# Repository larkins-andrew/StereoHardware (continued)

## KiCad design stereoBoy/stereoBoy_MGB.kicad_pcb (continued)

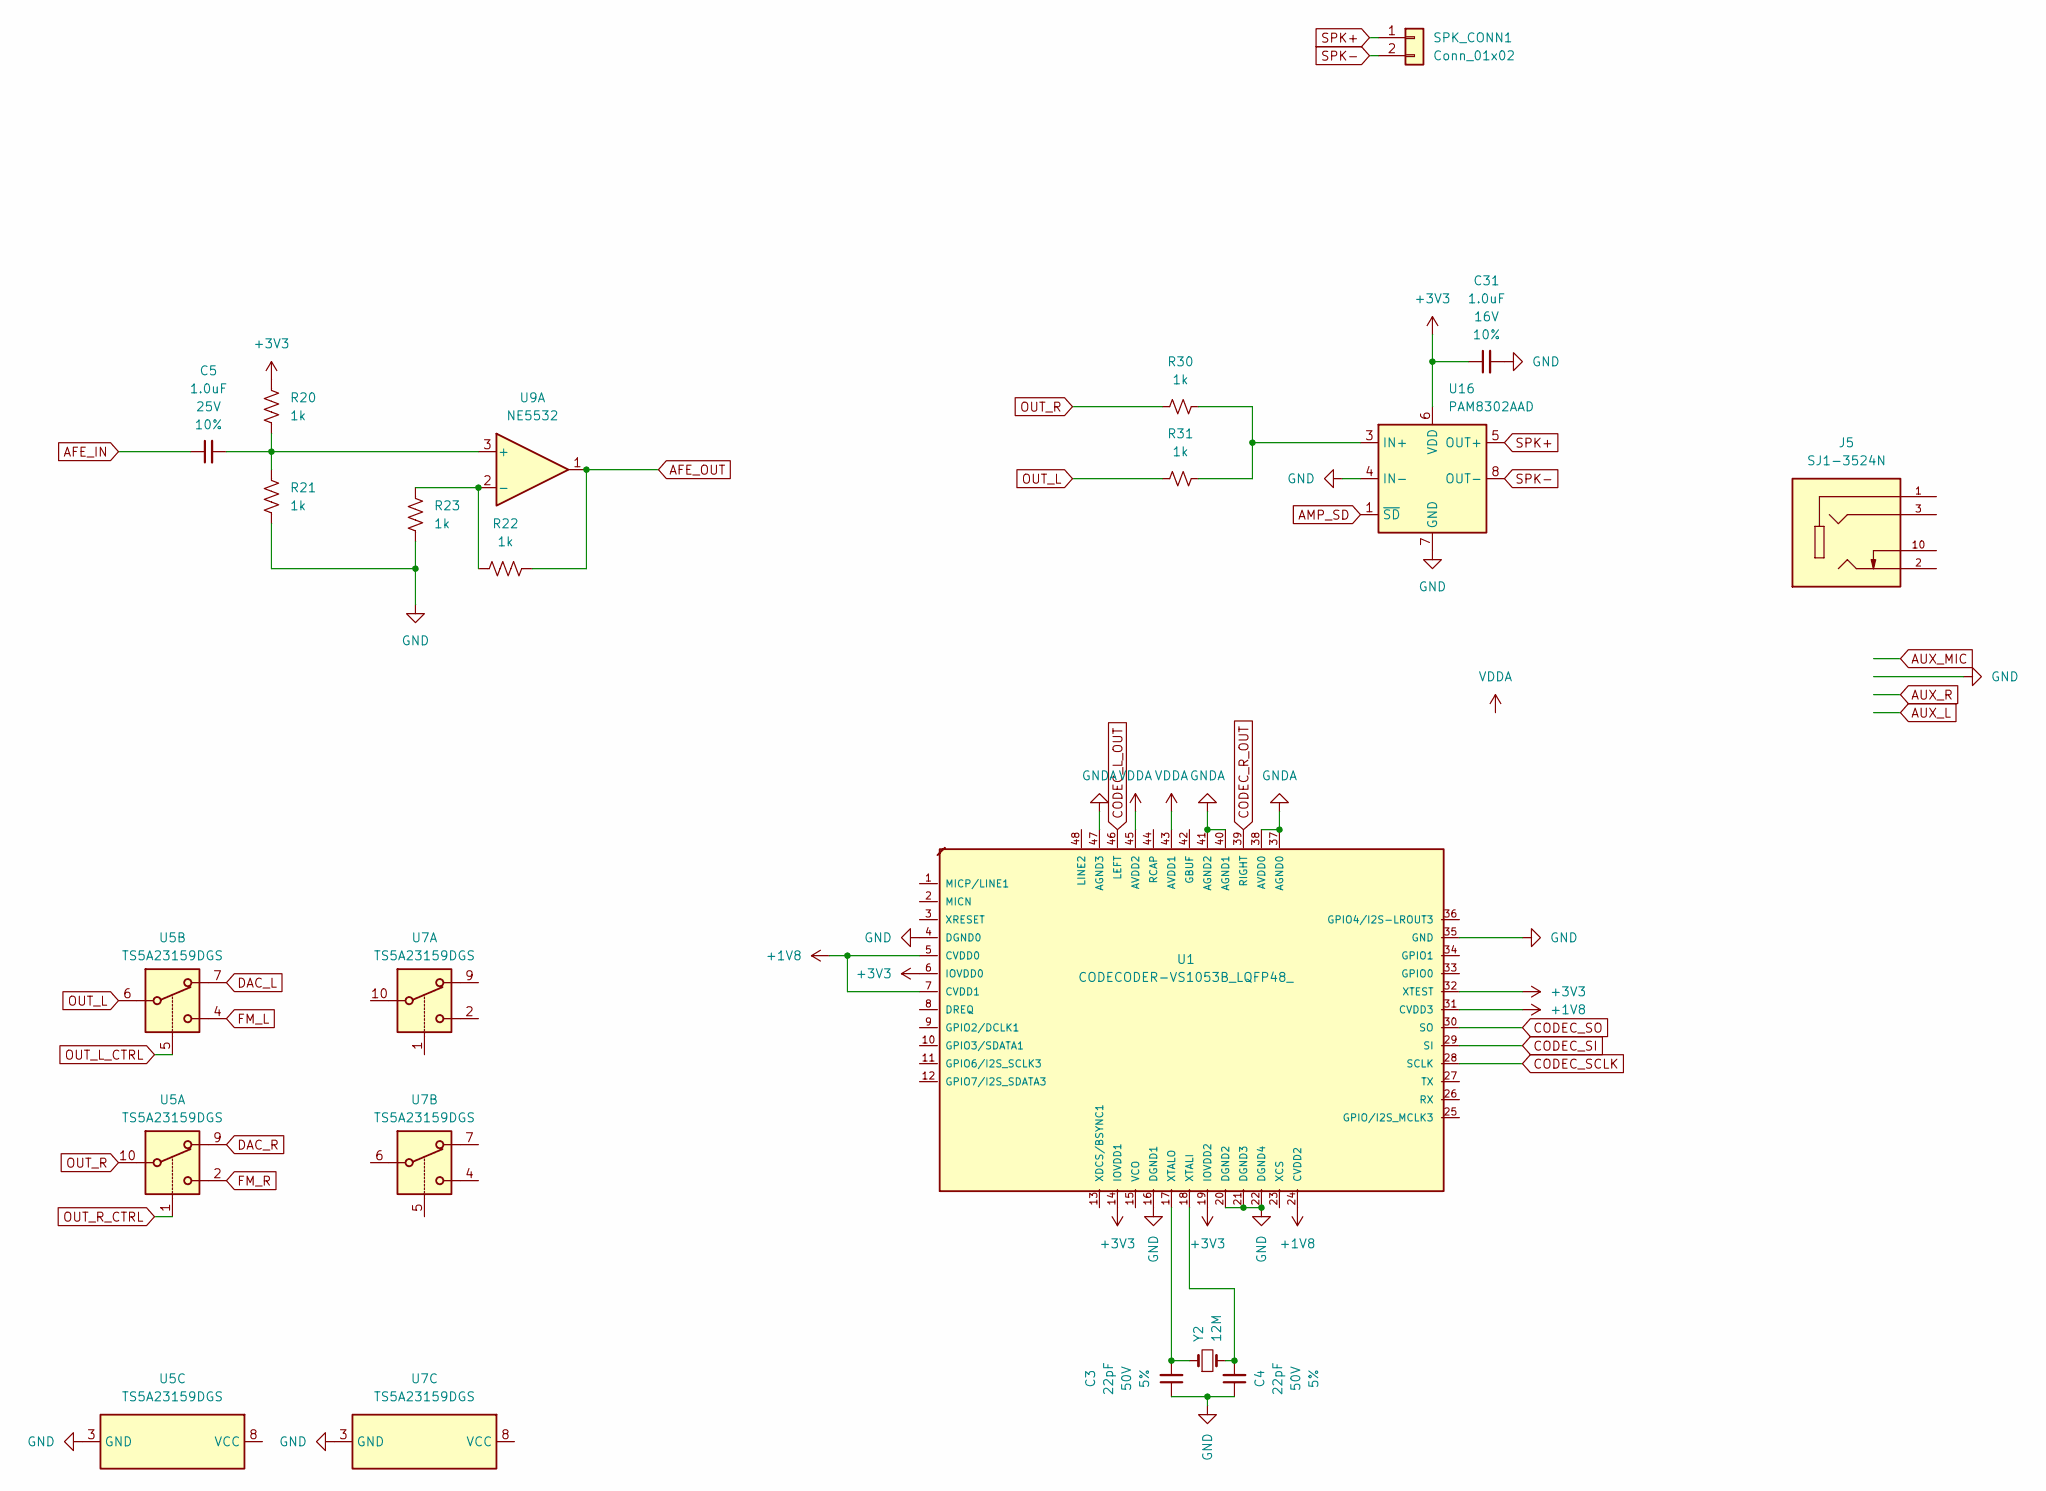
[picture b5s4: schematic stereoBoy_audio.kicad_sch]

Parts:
C3, C4: 22pF; C_0402_1005Metric; Voltage 50V; Tolerance 5%
C5: 1.0uF; C_0805_2012Metric; Voltage 25V; Tolerance 10%
C31: 1.0uF; C_0603_1608Metric; Voltage 16V; Tolerance 10%
J5: SJ1-3524N; PARTREV 1.05
R20, R21, R22, R23: 1k; R_0805_2012Metric
R30, R31: 1k; R_0603_1608Metric
SPK_CONN1: Conn_01x02; 1x02
U1: CODECODER-VS1053B_LQFP48_; VS1053b; MPN VS1053B
U5, U7: TS5A23159DGS; VSSOP-10_3x3mm_P0.5mm
U9: NE5532; SOIC-8_3.9x4.9mm_P1.27mm
U16: PAM8302AAD; MSOP-8_3x3mm_P0.65mm
Y2: 12M; Crystal_SMD_3.2x1.5mm

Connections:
+1V8: U1.5 (CVDD0), U1.7 (CVDD1), U1.24 (CVDD2), U1.31 (CVDD3); also elsewhere on the board
+3V3: C31.1, R20.1, U1.6 (IOVDD0), U1.14 (IOVDD1), U1.19 (IOVDD2), U1.32 (XTEST), U16.6 (VDD); also elsewhere on the board
AFE_IN: C5.1
AFE_OUT: R22.1, U9.1
AMP_SD: U16.1 (~SD)
CODEC_L_OUT: U1.46 (LEFT)
CODEC_R_OUT: U1.39 (RIGHT)
CODEC_SCLK: U1.28 (SCLK)
CODEC_SI: U1.29 (SI)
CODEC_SO: U1.30 (SO)
DAC_L: U5.7; also elsewhere on the board
DAC_R: U5.9; also elsewhere on the board
FM_L: U5.4
FM_R: U5.2
GND: C3.1, C4.1, C31.2, R21.2, R23.2, U1.4 (DGND0), U1.16 (DGND1), U1.20 (DGND2), U1.21 (DGND3), U1.22 (DGND4), U1.35 (GND), U5.3 (GND), U7.3 (GND), U16.4 (IN-), U16.7 (GND); also elsewhere on the board
GNDA: U1.37 (AGND0), U1.38 (AVDD0), U1.40 (AGND1), U1.41 (AGND2), U1.47 (AGND3); also elsewhere on the board
unnamed: C4.2, U1.18 (XTALI), Y2.2
unnamed: C3.2, U1.17 (XTALO), Y2.1
unnamed: C5.2, R20.2, R21.1, U9.3 (+)
unnamed: R22.2, R23.1, U9.2 (-)
unnamed: R30.2, R31.2, U16.3 (IN+)
OUT_L: R31.1, U5.6
OUT_L_CTRL: U5.5
OUT_R: R30.1, U5.10
OUT_R_CTRL: U5.1
SPK+: SPK_CONN1.1, U16.5 (OUT+)
SPK-: SPK_CONN1.2, U16.8 (OUT-)
VDDA: U1.43 (AVDD1), U1.45 (AVDD2); also elsewhere on the board

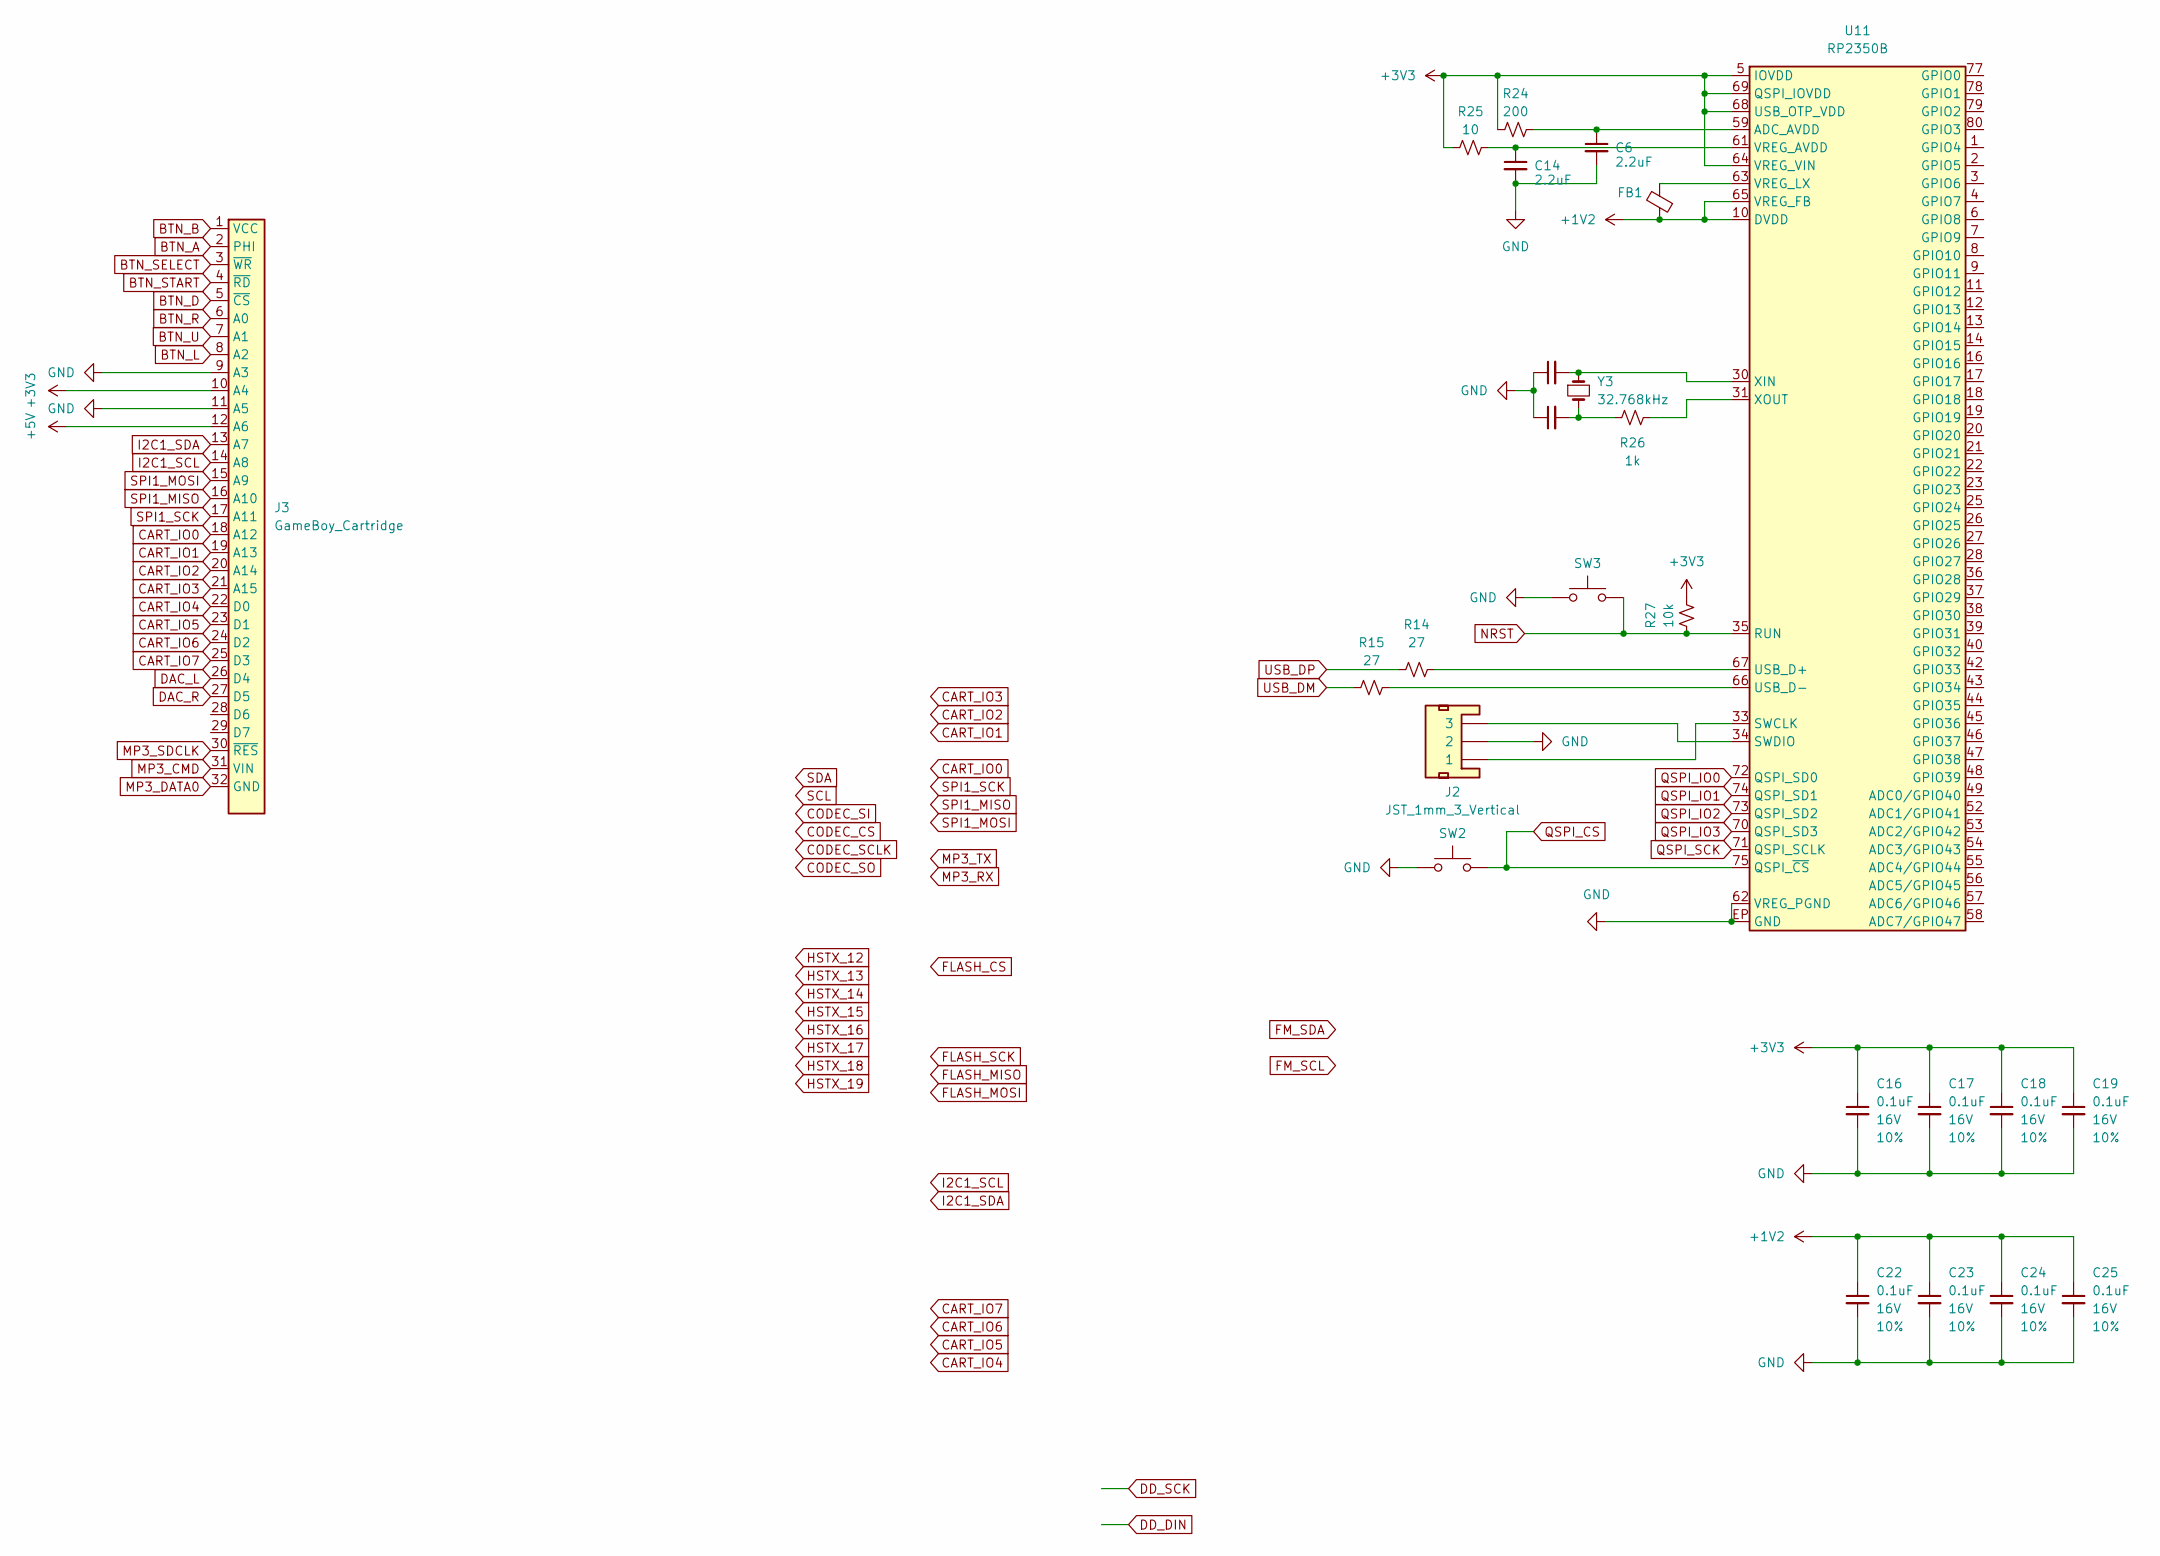
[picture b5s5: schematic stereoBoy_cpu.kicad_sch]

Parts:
C6, C14: 2.2uF; C_0402_1005Metric
C16, C17, C18, C19, C22, C23, C24, C25: 0.1uF; C_0402_1005Metric; Voltage 16V; Tolerance 10%
C20, C21: 18pF; C_0402_1005Metric; Voltage 50V; Tolerance 5%
FB1: FerriteBead_Small; L_0402_1005Metric
J2: JST_1mm_3_Vertical; JST_1x03_P1.0mm_Horizontal_SMD
J3: GameBoy_Cartridge; MGB-CART-CONN
R14, R15: 27; R_0402_1005Metric
R24: 200; R_0402_1005Metric
R25: 10; R_0402_1005Metric
R26: 1k; R_0402_1005Metric
R27: 10k; R_0603_1608Metric
SW2, SW3: SMD_4.2x3.2mm_h2.5mm; Push_SMD_4.2x3.2mm
U11: RP2350B; QFN-80-1EP_10x10mm_P0.4mm_EP3.4x3.4mm
Y3: 32.768kHz; Crystal_SMD_3.2x1.5mm

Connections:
+1V2: C22.1, C23.1, C24.1, C25.1, FB1.1, U11.10 (DVDD), U11.32 (DVDD), U11.51 (DVDD), U11.65 (VREG_FB)
+3V3: C16.1, C17.1, C18.1, C19.1, J3.10 (A4), R24.1, R25.1, R27.2, U11.5 (IOVDD), U11.15 (IOVDD), U11.24 (IOVDD), U11.29 (IOVDD), U11.41 (IOVDD), U11.50 (IOVDD), U11.60 (IOVDD), U11.64 (VREG_VIN), U11.68 (USB_OTP_VDD), U11.69 (QSPI_IOVDD), U11.76 (IOVDD); also elsewhere on the board
+5V: J3.12 (A6); also elsewhere on the board
BTN_A: J3.2 (PHI); also elsewhere on the board
BTN_B: J3.1 (VCC); also elsewhere on the board
BTN_D: J3.5 (~CS); also elsewhere on the board
BTN_L: J3.8 (A2); also elsewhere on the board
BTN_R: J3.6 (A0); also elsewhere on the board
BTN_SELECT: J3.3 (~WR); also elsewhere on the board
BTN_START: J3.4 (~RD); also elsewhere on the board
BTN_U: J3.7 (A1); also elsewhere on the board
CART_IO0: J3.18 (A12)
CART_IO1: J3.19 (A13)
CART_IO2: J3.20 (A14)
CART_IO3: J3.21 (A15)
CART_IO4: J3.22 (D0)
CART_IO5: J3.23 (D1)
CART_IO6: J3.24 (D2)
CART_IO7: J3.25 (D3)
DAC_L: J3.26 (D4); also elsewhere on the board
DAC_R: J3.27 (D5); also elsewhere on the board
GND: C6.2, C14.2, C16.2, C17.2, C18.2, C19.2, C20.1, C21.1, C22.2, C23.2, C24.2, C25.2, J2.2, J3.9 (A3), J3.11 (A5), SW2.1, SW3.1, U11.62 (VREG_PGND), U11.EP (GND); also elsewhere on the board
I2C1_SCL: J3.14 (A8)
I2C1_SDA: J3.13 (A7)
MP3_CMD: J3.31 (VIN)
MP3_DATA0: J3.32 (GND)
MP3_SDCLK: J3.30 (~RES)
NRST: R27.1, SW3.2, U11.35 (RUN)
unnamed: C21.2, R26.1, Y3.2
unnamed: C6.1, R24.2, U11.59 (ADC_AVDD)
unnamed: J2.1, U11.33 (SWCLK)
unnamed: J2.3, U11.34 (SWDIO)
unnamed: R14.2, U11.67 (USB_D+)
unnamed: R15.2, U11.66 (USB_D-)
unnamed: C14.1, R25.2, U11.61 (VREG_AVDD)
unnamed: FB1.2, U11.63 (VREG_LX)
unnamed: C20.2, U11.30 (XIN), Y3.1
unnamed: R26.2, U11.31 (XOUT)
QSPI_CS: SW2.2, U11.75 (QSPI_~CS)
QSPI_IO0: U11.72 (QSPI_SD0)
QSPI_IO1: U11.74 (QSPI_SD1)
QSPI_IO2: U11.73 (QSPI_SD2)
QSPI_IO3: U11.70 (QSPI_SD3)
QSPI_SCK: U11.71 (QSPI_SCLK)
SPI1_MISO: J3.16 (A10)
SPI1_MOSI: J3.15 (A9)
SPI1_SCK: J3.17 (A11)
USB_DM: R15.1; also elsewhere on the board
USB_DP: R14.1; also elsewhere on the board

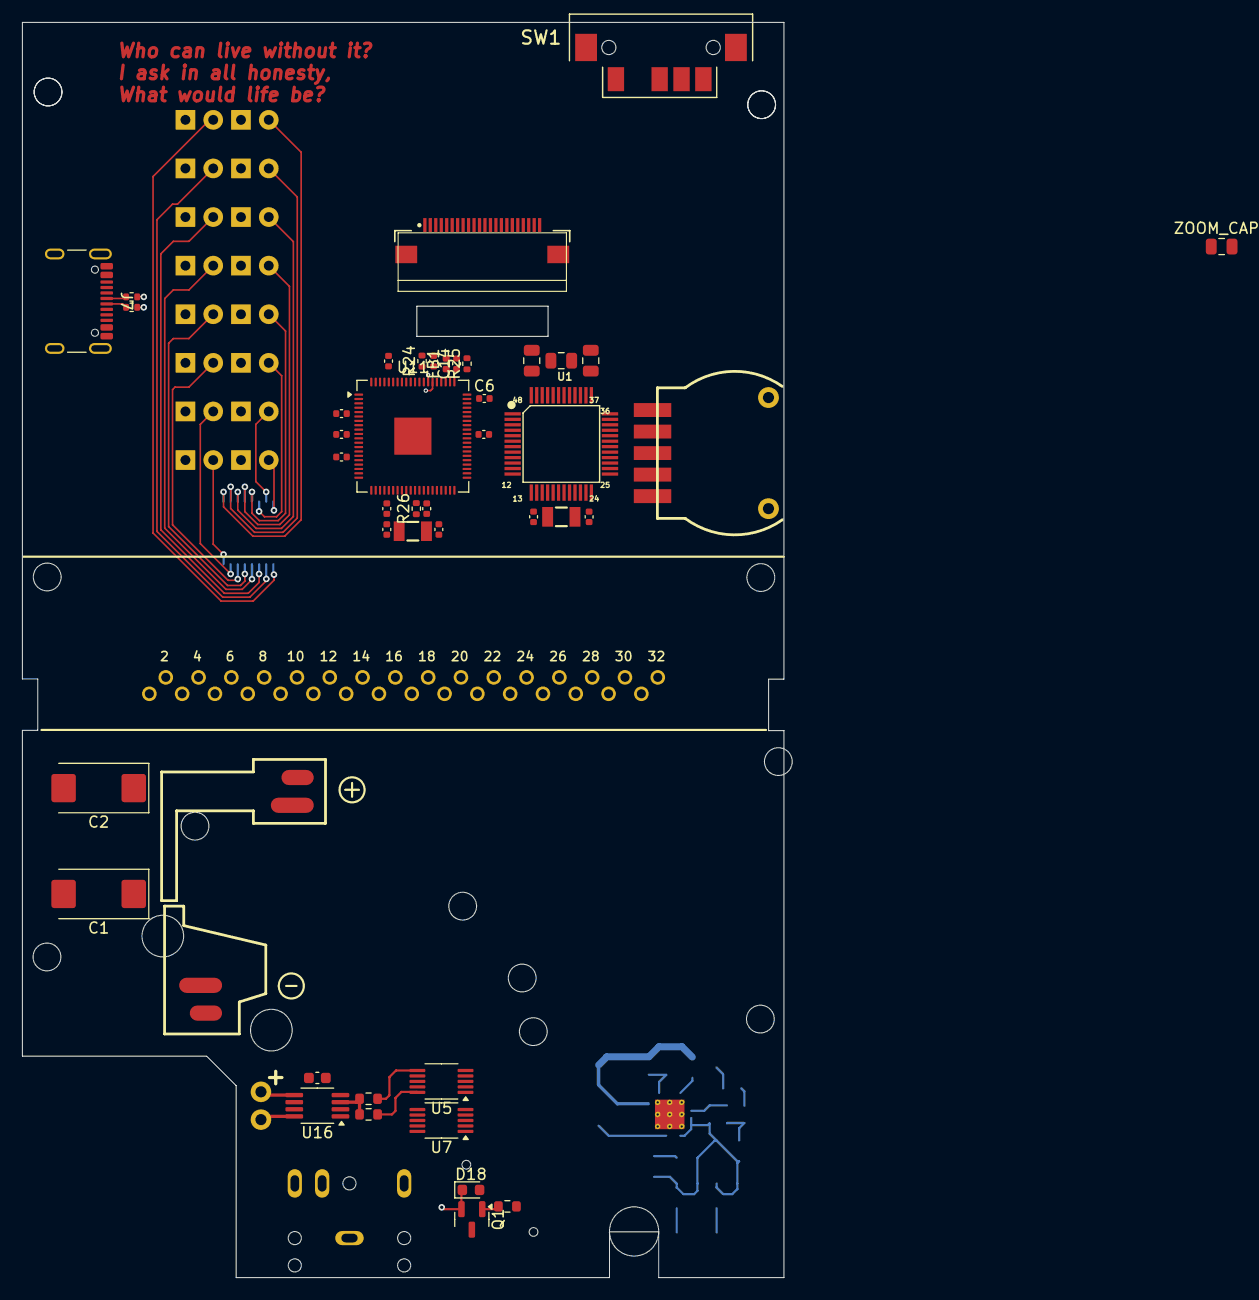
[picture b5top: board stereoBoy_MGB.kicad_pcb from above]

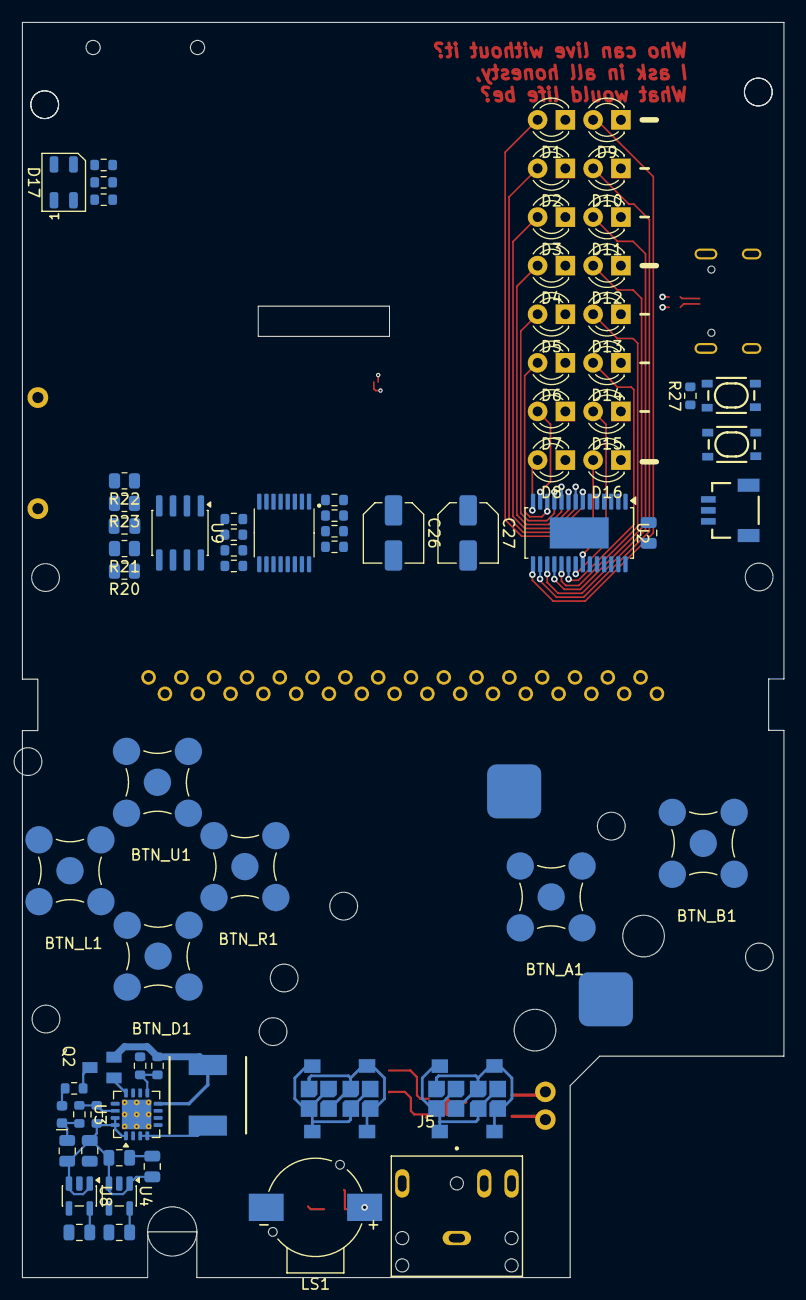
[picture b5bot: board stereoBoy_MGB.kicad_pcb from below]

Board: 4 copper layers, 69.6 x 114.8 mm, 130 parts (71 on the bottom side), 70 nets.

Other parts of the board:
1.54_IPS_LCD: 1.54_IPS_LCD
SW1: SMD_4.2x3.2mm_h2.5mm; MGB-SWITCH
UNK_HOLE_0: dummyfp0
UNK_HOLE_1: dummyfp1
UNK_HOLE_4: dummyfp4
UNK_HOLE_5: dummyfp5
UNK_HOLE_6: dummyfp6
UNK_HOLE_7: dummyfp7
UNK_HOLE_8: dummyfp8
UNK_HOLE_9: dummyfp9
UNK_HOLE_10: dummyfp10
UNK_HOLE_11: dummyfp11
UNK_HOLE_12: dummyfp12
UNK_HOLE_13: dummyfp13
VR1: MGB-POT

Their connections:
GND: VR1.P$1, VR1.P$6, VR1.P$7; also elsewhere on the board

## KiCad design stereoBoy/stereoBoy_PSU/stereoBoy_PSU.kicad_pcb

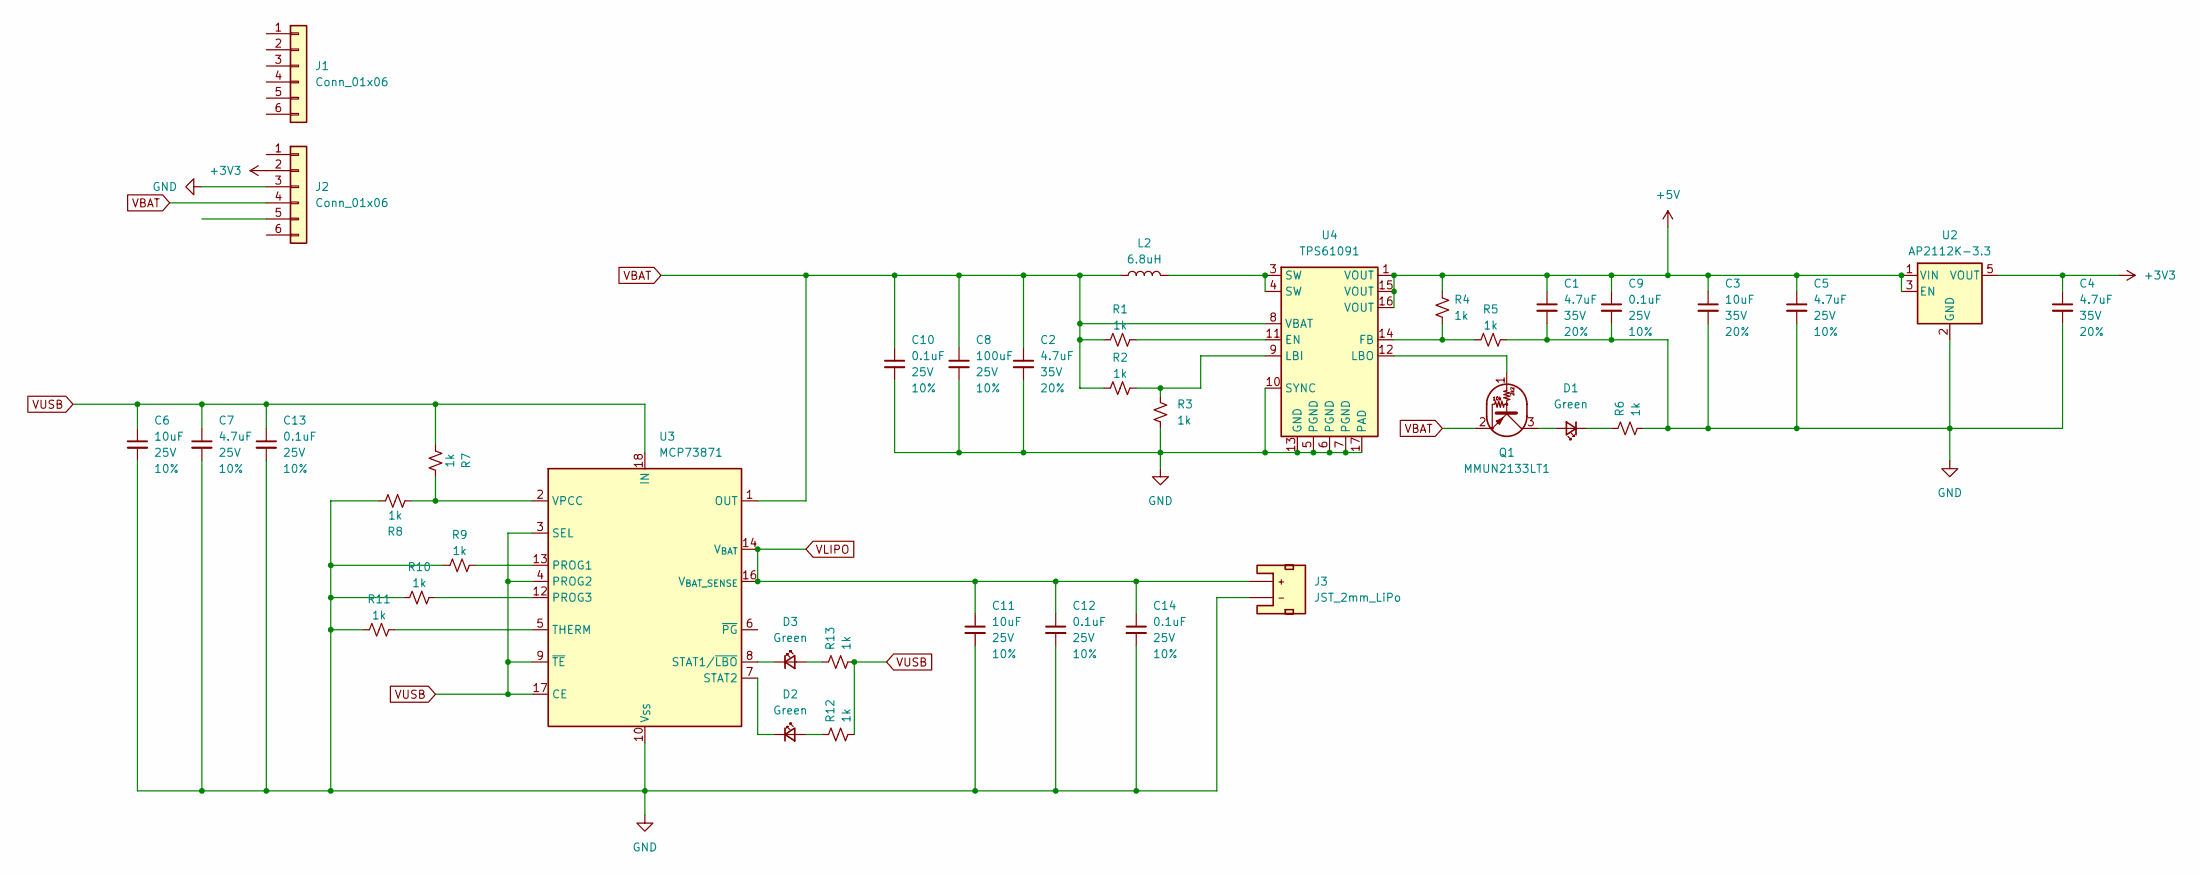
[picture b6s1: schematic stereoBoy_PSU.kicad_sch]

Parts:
C1, C2, C4: 4.7uF; C_0603_1608Metric; Voltage 35V; Tolerance 20%
C3: 10uF; C_0603_1608Metric; Voltage 35V; Tolerance 20%
C5, C7: 4.7uF; C_0805_2012Metric; Voltage 25V; Tolerance 10%
C6, C11: 10uF; C_0805_2012Metric; Voltage 25V; Tolerance 10%
C8: 100uF; C_0805_2012Metric; Voltage 25V; Tolerance 10%
C9, C10, C12, C13: 0.1uF; C_0805_2012Metric; Voltage 25V; Tolerance 10%
C14: 0.1uF; C_0603_1608Metric; Voltage 25V; Tolerance 10%
D1, D2, D3: Green; LED_0603_1608Metric_Green
J1, J2: Conn_01x06; 1x06
J3: JST_2mm_LiPo; JST_SMD_2.0mm-2
L2: 6.8uH; L_Sunltech_SLW40xx
Q1: MMUN2133LT1; SOT-23
R1, R2, R3, R4, R5, R6, R7, R8, R9, R10, R11, R12, R13: 1k; R_0603_1608Metric
U2: AP2112K-3.3; SOT-23-5
U3: MCP73871; QFN-20-1EP_4x4mm_P0.5mm_EP2.5x2.5mm
U4: TPS61091; Texas_RSA_VQFN-16-1EP_4x4mm_P0.65mm_EP2.7x2.7mm_ThermalVias

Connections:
+3V3: C4.1, J2.2, U2.5 (VOUT)
+5V: C1.1, C3.1, C5.1, C9.1, R4.2, U2.1 (VIN), U2.3 (EN), U4.1 (VOUT), U4.15 (VOUT), U4.16 (VOUT)
GND: C1.2, C2.2, C3.2, C4.2, C5.2, C6.2, C7.2, C8.2, C9.2, C10.2, C11.2, C12.2, C13.2, C14.2, J2.3, J3.1 (-), R3.1, R5.2, R6.1, R8.2, R9.1, R10.1, R11.1, U2.2 (GND), U3.10 (V_{SS}), U3.11 (V_{SS}), U3.21 (V_{SS}), U4.5 (PGND), U4.6 (PGND), U4.7 (PGND), U4.10 (SYNC), U4.13 (GND), U4.17 (PAD)
unnamed: D1.2 (A), Q1.3 (C)
unnamed: D1.1 (K), R6.2
unnamed: D2.2 (A), R12.2
unnamed: D2.1 (K), U3.7 (STAT2)
unnamed: D3.2 (A), R13.2
unnamed: D3.1 (K), U3.8 (STAT1/~LBO)
unnamed: L2.2, U4.3 (SW), U4.4 (SW)
unnamed: Q1.1 (B), U4.12 (LBO)
unnamed: R9.2, U3.13 (PROG1)
unnamed: R10.2, U3.12 (PROG3)
unnamed: R11.2, U3.5 (THERM)
unnamed: R7.2, R8.1, U3.2 (VPCC)
unnamed: R1.2, U4.11 (EN)
unnamed: R4.1, R5.1, U4.14 (FB)
unnamed: R2.1, R3.2, U4.9 (LBI)
VBAT: C2.1, C8.1, C10.1, J2.4, L2.1, Q1.2 (E), R1.1, R2.2, U3.1 (OUT), U3.20 (OUT), U4.8 (VBAT)
VLIPO: C11.1, C12.1, C14.1, J3.2 (+), U3.14 (V_{BAT}), U3.15 (V_{BAT}), U3.16 (V_{BAT_SENSE})
VUSB: C6.1, C7.1, C13.1, R7.1, R12.1, R13.1, U3.3 (SEL), U3.4 (PROG2), U3.9 (~TE), U3.17 (CE), U3.18 (IN), U3.19 (IN)

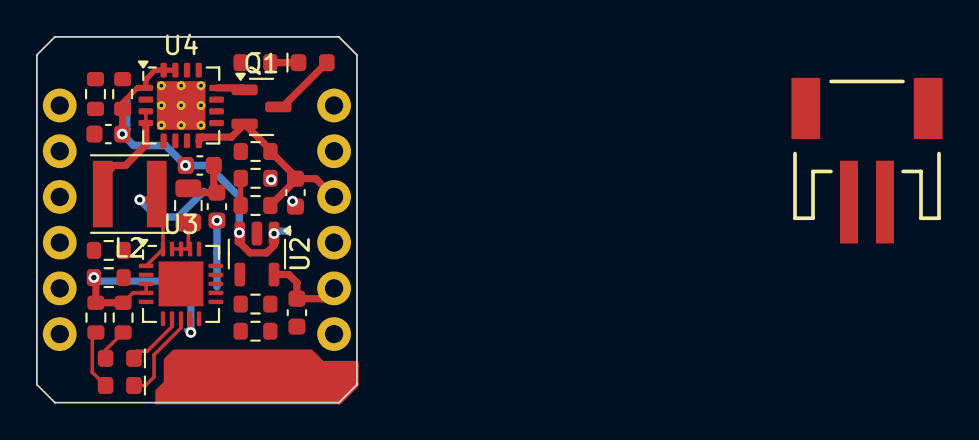
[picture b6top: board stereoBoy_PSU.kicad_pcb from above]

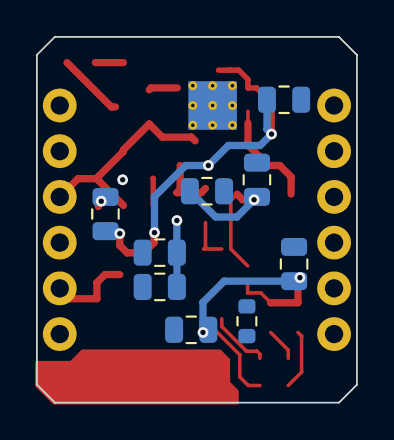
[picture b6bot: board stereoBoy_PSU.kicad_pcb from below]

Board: 2 copper layers, 17.8 x 20.3 mm, 38 parts (9 on the bottom side), 21 nets.

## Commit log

2025-10-16 asdf
2025-10-16 asdf
    asdf
2025-10-18 redesigned PSU for AAAs
2025-10-26 yeah
2026-02-25 New thingies
